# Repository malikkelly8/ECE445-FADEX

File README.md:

# FadeX - Automated Nicotine Tapering System

FadeX is an adaptive nicotine tapering prototype developed for ECE 445. The project explores a safer, feedback-based way to reduce nicotine concentration over time while preserving the user's familiar puff routine. Instead of forcing large manual concentration jumps, FadeX uses puff behavior, user check-ins, and embedded control logic to calculate a gradual taper and prepare a target mixture.

## Team Members

- **Malik Kelly** - Tapering algorithm, app/chatbot interface, ESP32 integration support
- **Justin Leith** - Project management, mechanical design, optical sensing support
- **Ian Zentner** - MCU logic, PCB design, hardware integration

## Final Prototype Overview

The final FadeX prototype centers on a **Homebase ESP32** that coordinates communication, dosing logic, pump control, load-cell feedback, and concentration sensing. A simplified **Handheld ESP32** is used to record puff activity and send puff-session data to the homebase. The system was demonstrated using a nicotine surrogate rather than real nicotine for safety.

The final architecture includes:

- **Homebase Controller:** ESP32-based controller that runs the tapering algorithm, receives puff data, controls pumps, reads load cells, and manages safety logic.
- **Handheld Puff Input:** Simplified ESP32 handheld with a puff button that records puff count/session duration and sends data to the homebase through ESP-NOW.
- **Fluid Delivery System:** Peristaltic pumps used to deliver concentrate/surrogate and diluent into a mixing reservoir.
- **Load-Cell Feedback:** HX711 load-cell amplifiers used to tare containers and verify delivered liquid mass.
- **UNCS Concentration Sensing:** UV LED and photodiode circuitry used to support concentration feedback for the vitamin C/ascorbic acid surrogate.
- **User Interface:** Blynk dashboard and/or serial-based FadeX Chatbot used to display system state, collect check-in responses, and guide the demo flow.

## Tapering Algorithm

FadeX calculates the next concentration using puff behavior, treatment week, user survey feedback, and safety limits. The algorithm combines objective usage data with simple self-report inputs so that the taper can slow down or stabilize when relapse risk appears higher.

Core algorithm ideas:

- Puff count and puff duration are collected from the handheld or demo input.
- The user check-in classifies the session as `Better`, `Neutral`, `Struggling`, or `Worse`.
- Trigger questions are only asked when the user reports `Struggling` or `Worse`.
- Scenario codes classify the current user state and guide tapering behavior.
- The next concentration is safety-clamped before pump volumes are calculated.
- Pump delivery is verified using load-cell feedback instead of relying only on timed pumping.

Example equations:

```text
A = 1.0 + S + (1.0 - Mu)
C_next = clamp(C_current - 0.28A, 0.5%, 5.0%)
V_concentrate = (C_next / 5.0) * V_total
V_diluent = V_total - V_concentrate
```

## Repository Structure

```text
/Code/              Firmware sketches, tests, and integration code
/Images/            Diagrams, presentation graphics, screenshots, and verification visuals
/Notebook_Entries/  Chronological lab notebook entries and engineering logs
/PCB/          PCB schematics, pinout references, and hardware design files
```

Some folders may contain uploaded final report materials, figures, or archived versions of earlier designs.

## Key Subsystem Tests

The project was developed through modular tests before final integration:

- ESP32 programming and MAC address identification
- ESP-NOW handheld-to-homebase puff communication
- Pump direction, flow-rate, and volume delivery tests
- Load-cell calibration and tare verification
- Water-by-weight dispense testing
- UV LED PWM output testing
- Photodiode ADC readout testing
- Blynk dashboard and FadeX Chatbot workflow testing
- Final integrated dosing and demo flow testing

## Safety Notes

The course prototype used water and vitamin C/ascorbic acid surrogate solutions instead of nicotine for safety. The firmware and demo flow include safety-oriented behavior such as load-cell taring, staged pump pulses, maximum mixing-volume checks, and emergency stop commands. The homebase controller is responsible for safety-critical pump control rather than relying only on the app interface.

## Project Tracking and Engineering Notebook

- `/Notebook_Entries/` contains chronological lab notebook entries documenting objectives, design decisions, testing, debugging, and final outcomes.
- `/Images/` contains visuals used for reports, slides, flowcharts, and verification documentation.
- The GitHub Project/Kanban board was used during development to track subsystem progress and remaining demo tasks.

## Final Deliverables

Final project materials include the final paper, video assignment, lab notebook entries, subsystem test code, algorithm visuals, and final demo documentation.

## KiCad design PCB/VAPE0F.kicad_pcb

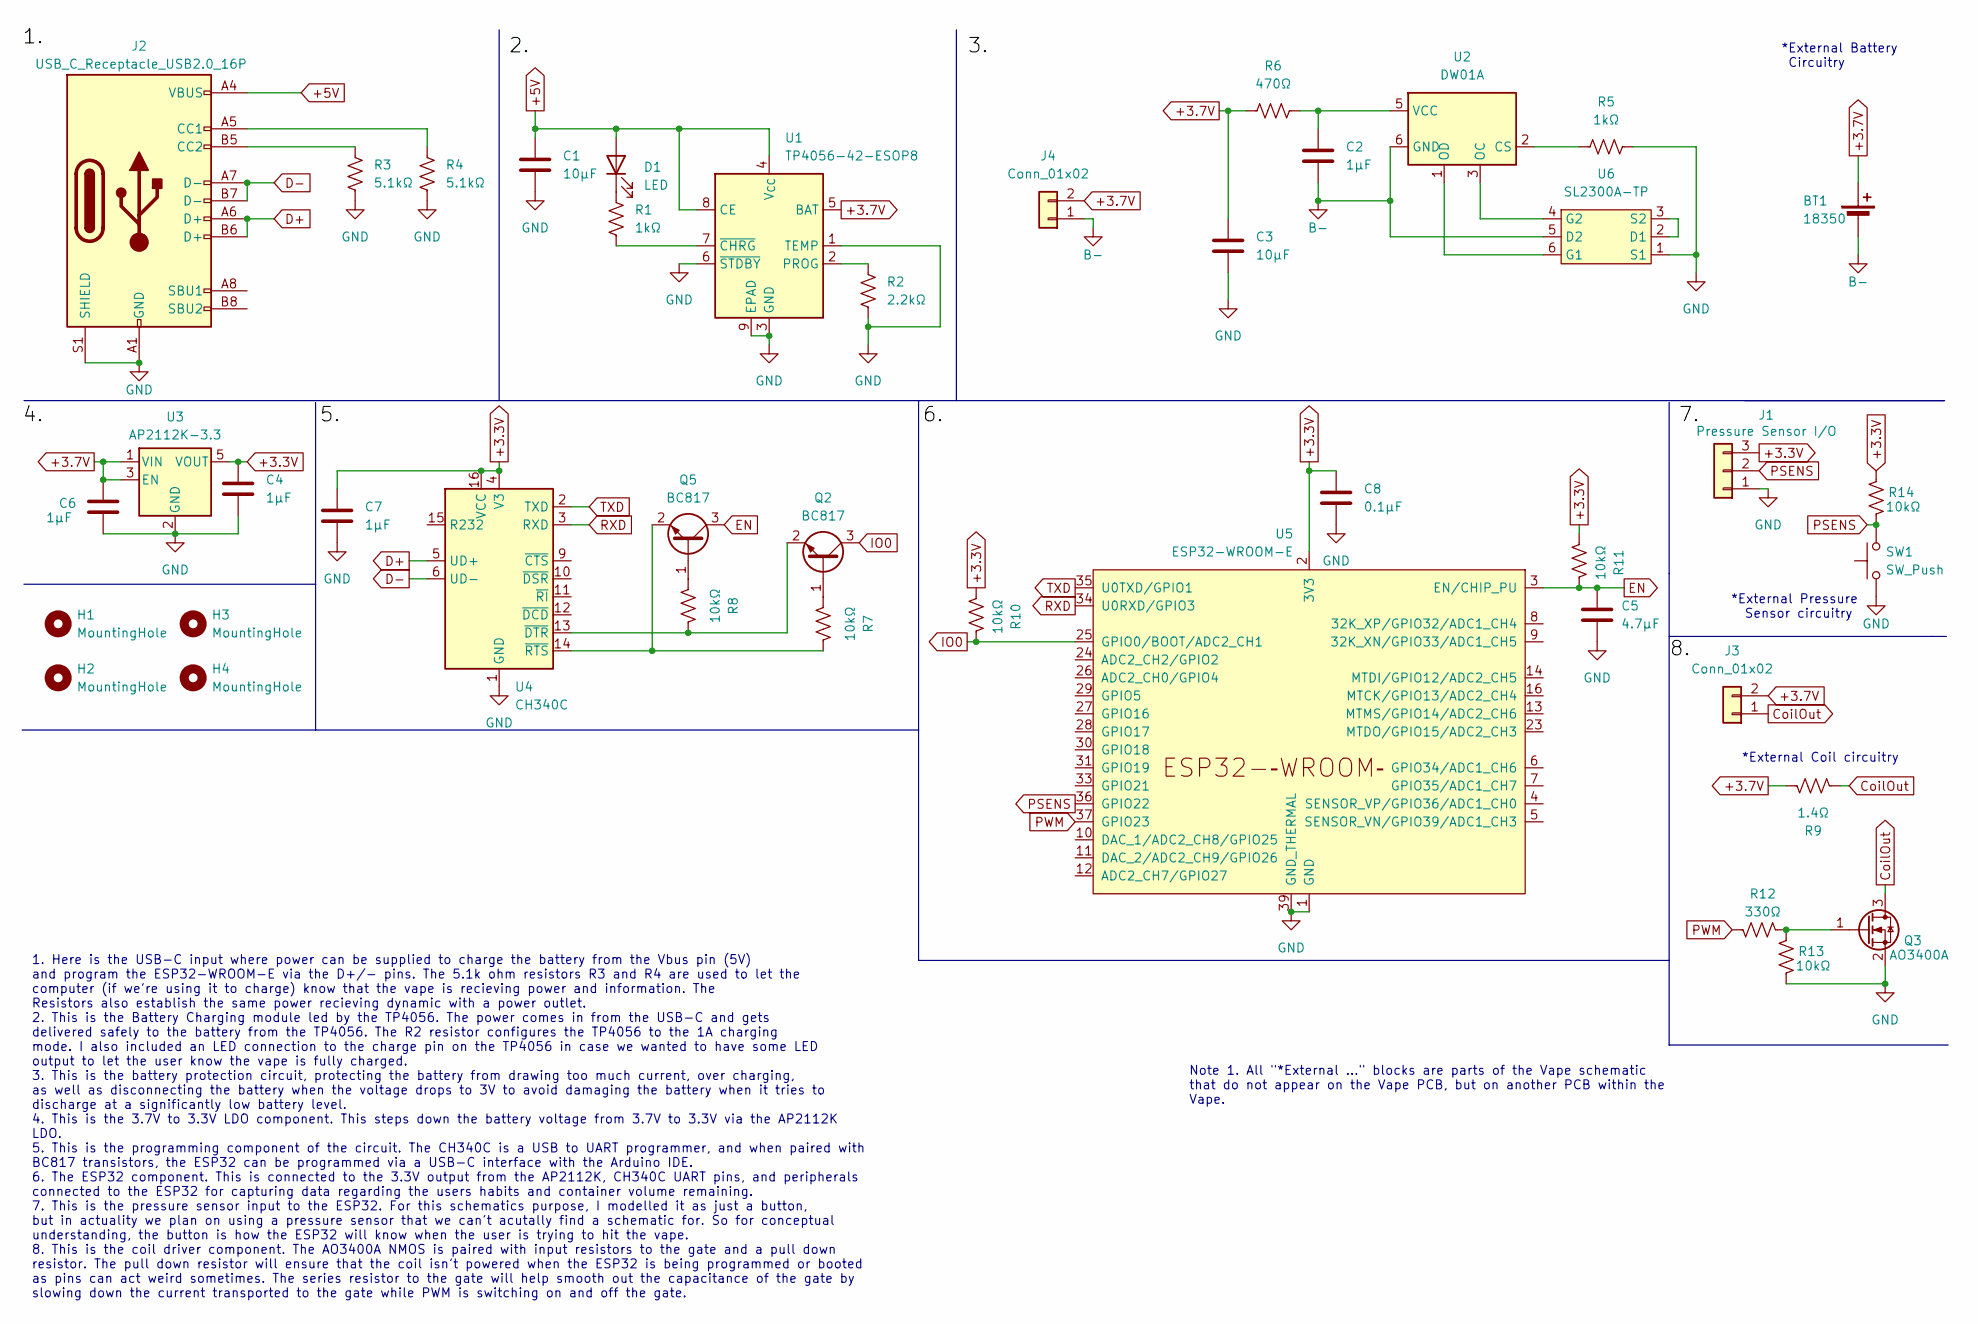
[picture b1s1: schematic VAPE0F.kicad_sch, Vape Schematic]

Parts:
BT1: 18350
C1, C3: 10μF; C_0805_2012Metric_Pad1.18x1.45mm_HandSolder
C2, C4, C6, C7: 1μF; C_0805_2012Metric_Pad1.18x1.45mm_HandSolder
C5: 4.7μF; C_0805_2012Metric_Pad1.18x1.45mm_HandSolder
C8: 0.1μF; C_0805_2012Metric_Pad1.18x1.45mm_HandSolder
D1: LED; LED_0805_2012Metric_Pad1.15x1.40mm_HandSolder
H1, H2, H3, H4: MountingHole; MountingHole_3.2mm_M3
J1: Pressure Sensor I/O; Molex_KK-254_AE-6410-03A_1x03_P2.54mm_Vertical
J2: USB_C_Receptacle_USB2.0_16P; USB_C_Receptacle_HRO_TYPE-C-31-M-12
J3, J4: Conn_01x02; Molex_KK-254_AE-6410-02A_1x02_P2.54mm_Vertical
Q2, Q5: BC817; SOT-23
Q3: AO3400A; SOT-23
R1, R5: 1kΩ; R_0805_2012Metric_Pad1.20x1.40mm_HandSolder
R2: 2.2kΩ; R_0805_2012Metric_Pad1.20x1.40mm_HandSolder
R3, R4: 5.1kΩ; R_0805_2012Metric_Pad1.20x1.40mm_HandSolder
R6: 470Ω; R_0805_2012Metric_Pad1.20x1.40mm_HandSolder
R7, R8, R10, R11, R13, R14: 10kΩ; R_0805_2012Metric_Pad1.20x1.40mm_HandSolder
R9: 1.4Ω; R_0805_2012Metric_Pad1.20x1.40mm_HandSolder
R12: 330Ω; R_0805_2012Metric_Pad1.20x1.40mm_HandSolder
SW1: SW_Push
U1: TP4056-42-ESOP8; SOIC-8-1EP_3.9x4.9mm_P1.27mm_EP2.41x3.3mm_ThermalVias
U2: DW01A; SOT-23-6
U3: AP2112K-3.3; SOT-23-5
U4: CH340C; SOIC-16_3.9x9.9mm_P1.27mm
U5: ESP32-WROOM-E; ESP32-WROOM-32E
U6: SL2300A-TP; SOT-23-6_Handsoldering

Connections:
+3.3V: C4.1, C7.1, C8.1, J1.3, R10.2, R11.2, R14.2, U3.5 (VOUT), U4.4 (V3), U4.16 (VCC), U5.2 (3V3)
+3.7V: BT1.1 (+), C3.1, C6.1, J3.2, J4.2, R6.1, R9.1, U1.5 (BAT), U3.1 (VIN), U3.3 (EN)
+5V: C1.1, D1.2 (A), J2.A4 (VBUS), J2.A9 (VBUS), J2.B4 (VBUS), J2.B9 (VBUS), U1.4 (V_{CC}), U1.8 (CE)
B-: BT1.2 (-), C2.2, J4.1, U2.6 (GND), U6.5 (D2)
CoilOut: J3.1, Q3.3 (D), R9.2
D+: J2.A6 (D+), J2.B6 (D+), U4.5 (UD+)
D-: J2.A7 (D-), J2.B7 (D-), U4.6 (UD-)
EN: C5.1, Q5.3 (C), R11.1, U5.3 (EN/CHIP_PU)
GND: C1.2, C3.2, C4.2, C5.2, C6.2, C7.2, C8.2, J1.1, J2.A1 (GND), J2.A12 (GND), J2.B1 (GND), J2.B12 (GND), J2.S1 (SHIELD), Q3.2 (S), R2.2, R3.2, R4.2, R5.2, R13.1, SW1.1, U1.1 (TEMP), U1.3 (GND), U1.6 (~STDBY), U1.9 (EPAD), U3.2 (GND), U4.1 (GND), U5.1 (GND), U5.15 (GND), U5.38 (GND), U5.39 (GND_THERMAL), U6.1 (S1)
IO0: Q2.3 (C), R10.1, U5.25 (GPIO0/BOOT/ADC2_CH1)
unnamed: D1.1 (K), R1.1
unnamed: J2.A5 (CC1), R4.1
unnamed: J2.B5 (CC2), R3.1
unnamed: Q2.1 (B), R7.2
unnamed: Q2.2 (E), R8.1, U4.13 (~DTR)
unnamed: Q3.1 (G), R12.2, R13.2
unnamed: Q5.1 (B), R8.2
unnamed: Q5.2 (E), R7.1, U4.14 (~RTS)
unnamed: R2.1, U1.2 (PROG)
unnamed: R1.2, U1.7 (~CHRG)
unnamed: R5.1, U2.2 (CS)
unnamed: U2.3 (OC), U6.4 (G2)
unnamed: U2.1 (OD), U6.6 (G1)
unnamed: C2.1, R6.2, U2.5 (VCC)
unnamed: U6.2 (D1), U6.3 (S2)
PSENS: J1.2, R14.1, SW1.2, U5.36 (GPIO22)
PWM: R12.1, U5.37 (GPIO23)
RXD: U4.3 (RXD), U5.34 (U0RXD/GPIO3)
TXD: U4.2 (TXD), U5.35 (U0TXD/GPIO1)

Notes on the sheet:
*External Coil circuitry
*External Battery Circuitry
1. Here is the USB-C input where power can be supplied to charge the battery from the Vbus pin (5V) and program the ESP32-WROOM-E via the D+/- pins. The 5.1k ohm resistors R3 and R4 are used to let the computer (if we're using it to charge) know that the vape is recieving power and information. The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
Note 1. All "*External ..." blocks are parts of the Vape schematic that do not appear on the Vape PCB, but on another PCB within the Vape.
*External Pressure Sensor circuitry

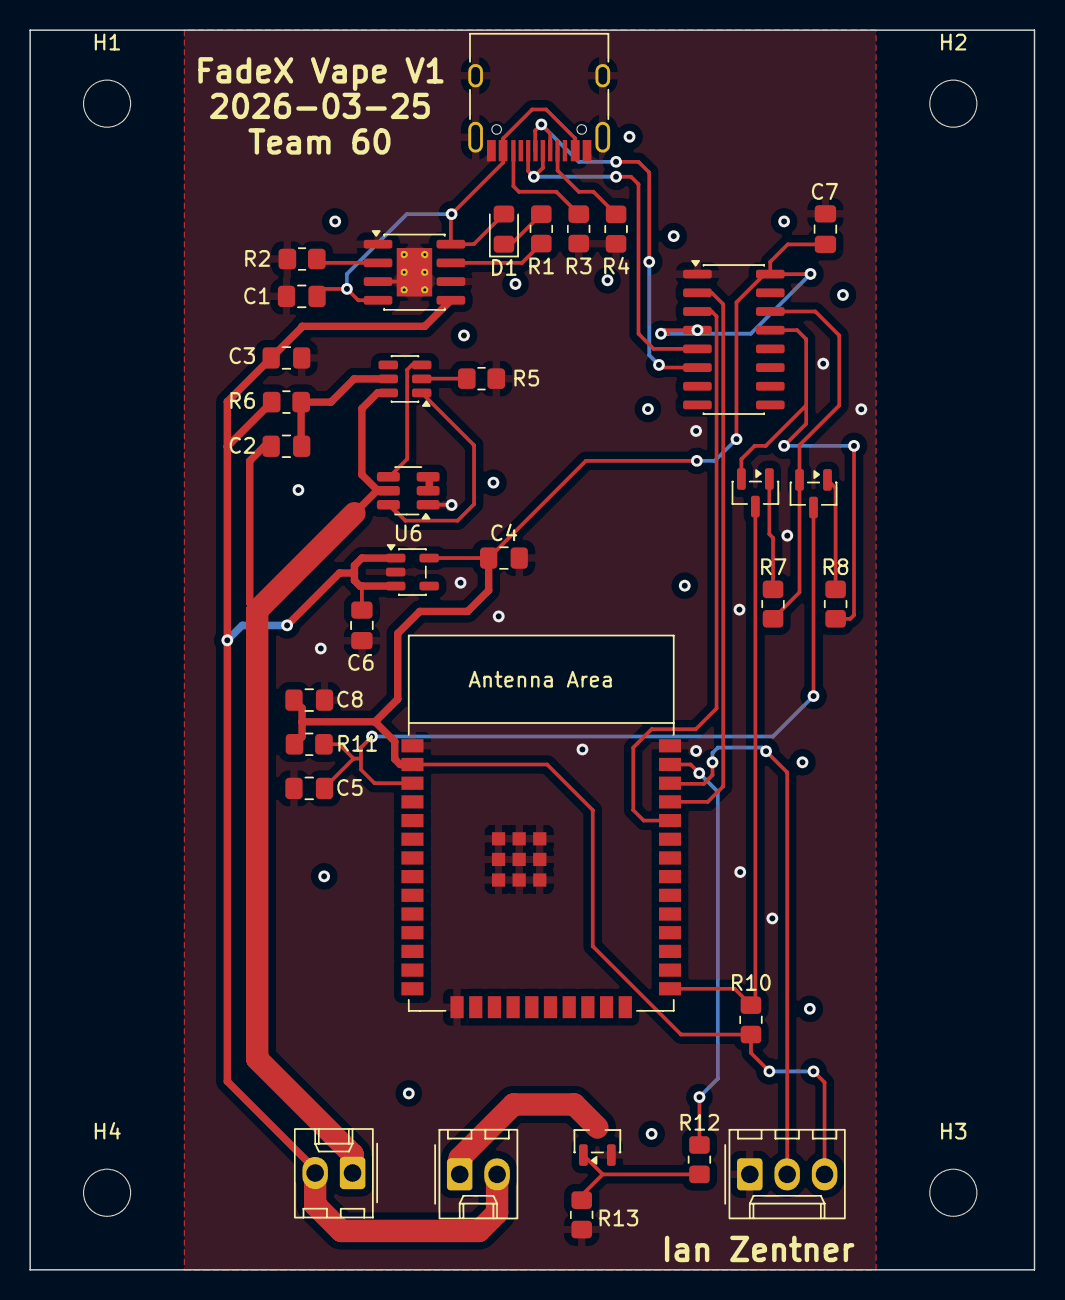
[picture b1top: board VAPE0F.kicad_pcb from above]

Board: 2 copper layers, 68.2 x 84.2 mm, 38 parts (0 on the bottom side), 29 nets.

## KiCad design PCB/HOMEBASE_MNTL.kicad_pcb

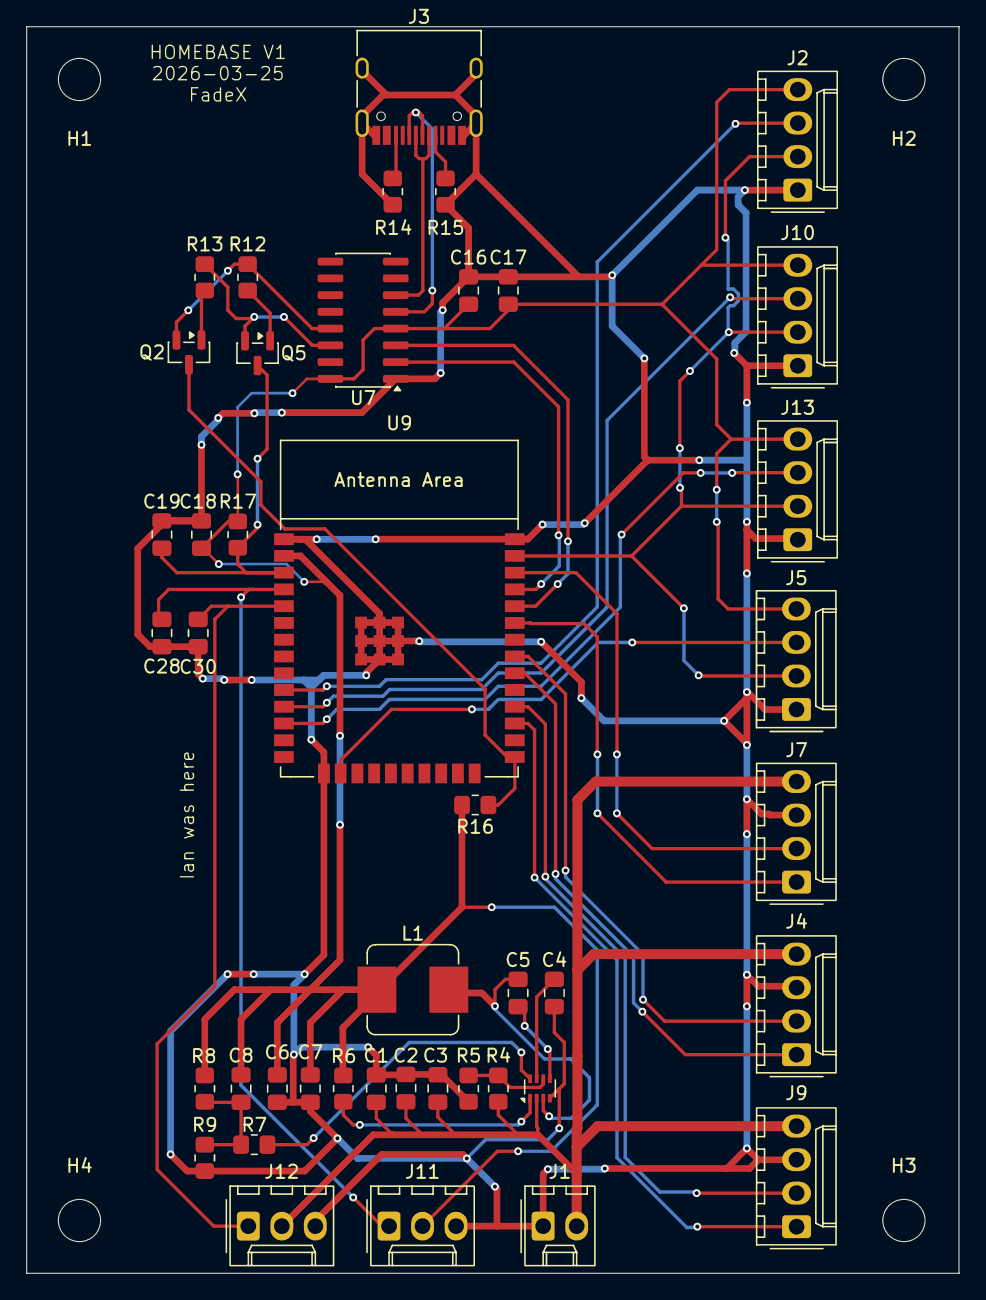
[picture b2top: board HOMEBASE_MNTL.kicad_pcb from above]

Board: 2 copper layers, 70.7 x 94.5 mm, 47 parts (0 on the bottom side), 36 nets.

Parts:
C1, C2: 10μF; C_0805_2012Metric_Pad1.18x1.45mm_HandSolder
C3, C5, C18: 0.1μF; C_0805_2012Metric_Pad1.18x1.45mm_HandSolder
C4: 22nF; C_0805_2012Metric_Pad1.18x1.45mm_HandSolder
C6, C7: 22μF; C_0805_2012Metric_Pad1.18x1.45mm_HandSolder
C8: 470pF; C_0805_2012Metric_Pad1.18x1.45mm_HandSolder
C16, C17, C28, C30: 1μF; C_0805_2012Metric_Pad1.18x1.45mm_HandSolder
C19: 4.7μF; C_0805_2012Metric_Pad1.18x1.45mm_HandSolder
H1, H2, H3, H4: MountingHole; MountingHole_3.2mm_M3
J1: Conn_01x02; Molex_KK-254_AE-6410-02A_1x02_P2.54mm_Vertical
J2: Load Cell 1 Con.; Molex_KK-254_AE-6410-04A_1x04_P2.54mm_Vertical
J3: USB_C_Receptacle_USB2.0_16P; USB_C_Receptacle_HRO_TYPE-C-31-M-12
J4: Pump 2 Con.; Molex_KK-254_AE-6410-04A_1x04_P2.54mm_Vertical
J5: Load Cell 4 Con.; Molex_KK-254_AE-6410-04A_1x04_P2.54mm_Vertical
J7: Pump 1 Con.; Molex_KK-254_AE-6410-04A_1x04_P2.54mm_Vertical
J9: Pump 3 Con.; Molex_KK-254_AE-6410-04A_1x04_P2.54mm_Vertical
J10: Load Cell 2 Con.; Molex_KK-254_AE-6410-04A_1x04_P2.54mm_Vertical
J11: Photodiode Con.; Molex_KK-254_AE-6410-03A_1x03_P2.54mm_Vertical
J12: UVLED Con.; Molex_KK-254_AE-6410-03A_1x03_P2.54mm_Vertical
J13: Load Cell 3 Con.; Molex_KK-254_AE-6410-04A_1x04_P2.54mm_Vertical
L1: 6.8μH; L_Bourns_SRP7028A_7.3x6.6mm
Q2, Q5: BC817; SOT-23
R4: 191kΩ; R_0805_2012Metric_Pad1.20x1.40mm_HandSolder
R5: 49.9kΩ; R_0805_2012Metric_Pad1.20x1.40mm_HandSolder
R6: 100kΩ; R_0805_2012Metric_Pad1.20x1.40mm_HandSolder
R7, R12, R13, R16, R17: 10kΩ; R_0805_2012Metric_Pad1.20x1.40mm_HandSolder
R8: 51kΩ; R_0805_2012Metric_Pad1.20x1.40mm_HandSolder
R9: 9.09kΩ; R_0805_2012Metric_Pad1.20x1.40mm_HandSolder
R14, R15: 5.1kΩ; R_0805_2012Metric_Pad1.20x1.40mm_HandSolder
U2: MP2338GTL-P; SOT-583-8
U7: CH340C; SOIC-16_3.9x9.9mm_P1.27mm
U9: ESP32-WROOM-E; ESP32-WROOM-32E

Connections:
3.3V: C6.1, C7.1, C8.2, C16.1, C17.1, C18.1, J2.4, J5.4, J10.4, J11.2, J13.4, L1.2, R6.2, R8.2, R16.2, R17.2, U7.4 (V3), U7.16 (VCC), U9.2 (3V3)
12V: C1.1, C2.1, C3.1, J1.2, J4.4, J7.4, J9.4, J12.2, R4.1, U2.2 (VIN)
3190.1.IN1: J7.2, U9.36 (GPIO22)
3190.1.IN2: J7.1, U9.33 (GPIO21)
3190.2.IN1: J4.2, U9.31 (GPIO19)
3190.2.IN2: J4.1, U9.30 (GPIO18)
3190.3.IN1: J9.2, U9.28 (GPIO17)
3190.3.IN2: J9.1, U9.27 (GPIO16)
BST.3_3V: C5.1, U2.5 (BST)
D+: J3.A6 (D+), J3.B6 (D+), U7.5 (UD+)
D-: J3.A7 (D-), J3.B7 (D-), U7.6 (UD-)
DAT1: J2.3, U9.10 (DAC_1/ADC2_CH8/GPIO25)
DAT2: J10.3, U9.11 (DAC_2/ADC2_CH9/GPIO26)
DAT3: J13.3, U9.12 (ADC2_CH7/GPIO27)
DAT4: J5.3, U9.16 (MTCK/GPIO13/ADC2_CH4)
EN: C19.1, Q5.3 (C), R17.1, U9.3 (EN/CHIP_PU)
EN.3_3V: R4.2, R5.1, U2.6 (EN)
FB.3_3V: R7.1, U2.8 (FB)
GND: C1.2, C2.2, C3.2, C4.2, C6.2, C7.2, C16.2, C17.2, C18.2, C19.2, C28.2, C30.2, J1.1, J2.1, J3.A1 (GND), J3.A12 (GND), J3.B1 (GND), J3.B12 (GND), J3.S1 (SHIELD), J4.3, J5.1, J7.3, J9.3, J10.1, J11.3, J12.3, J13.1, R5.2, R9.2, R14.2, R15.2, U2.4 (GND), U7.1 (GND), U9.1 (GND), U9.15 (GND), U9.38 (GND), U9.39 (GND_THERMAL)
IO0: Q2.3 (C), R16.1, U9.25 (GPIO0/BOOT/ADC2_CH1)
unnamed: C8.1, R7.2, R8.1, R9.1
unnamed: J3.A5 (CC1), R15.1
unnamed: J3.B5 (CC2), R14.1
unnamed: J3.A4 (VBUS), J3.A9 (VBUS), J3.B4 (VBUS), J3.B9 (VBUS)
unnamed: Q2.1 (B), R13.2
unnamed: Q2.2 (E), R12.1, U7.13 (~DTR)
unnamed: Q5.1 (B), R12.2
unnamed: Q5.2 (E), R13.1, U7.14 (~RTS)
unnamed: C4.1, U2.7 (SS)
PDO: C28.1, J11.1, U9.4 (SENSOR_VP/GPIO36/ADC1_CH0)
PG.3_3V: R6.1, U2.1 (PG)
RXD: U7.3 (RXD), U9.34 (U0RXD/GPIO3)
SCLK: J2.2, J5.2, J10.2, J13.2, U9.37 (GPIO23)
SW.3_3V: C5.2, L1.1, U2.3 (SW)
TXD: U7.2 (TXD), U9.35 (U0TXD/GPIO1)
UVLEDPWM: C30.1, J12.1, U9.5 (SENSOR_VN/GPIO39/ADC1_CH3)

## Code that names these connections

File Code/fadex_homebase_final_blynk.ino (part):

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};

// Final PCB pump-driver wiring:
// Pump 1 (nicotine) -> IN1 GPIO22, IN2 GPIO21
// Pump 2 (diluent)  -> IN1 GPIO19, IN2 GPIO18
// Pump 3 (mixing)   -> IN1 GPIO33, IN2 GPIO4
constexpr PumpChannel NICOTINE_PUMP = {22, 21, "Nicotine"};
constexpr PumpChannel DILUENT_PUMP = {19, 18, "Diluent"};
constexpr PumpChannel MIXING_PUMP = {33, 4, "Mixing"};

// Final PCB load-cell wiring:
// Shared HX711 clock -> GPIO23
// Data lines -> GPIO25, GPIO26, GPIO27, GPIO13
constexpr int HX711_SCK_PIN = 23;
constexpr int HX711_DATA1_PIN = 25;
constexpr int HX711_DATA2_PIN = 26;
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
// UNCS optical sensor wiring:
// PDO is the photodiode/TIA output into ESP32 ADC1_CH0.
// UVLEDPWM needs an output-capable pin. The PCB net was originally tied to
// GPIO39, which is input-only, so the demo assumes the jumper to GPIO32.
constexpr int UNCS_PHOTODIODE_ADC_PIN = 36;
constexpr int UNCS_UV_LED_PWM_PIN = 32;
constexpr uint8_t UNCS_PWM_CHANNEL = 0;
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  setUncsLed(false);

  Serial.println("UNCS optical sensor initialized.");
  Serial.print("  Photodiode PDO ADC: GPIO");
  Serial.println(UNCS_PHOTODIODE_ADC_PIN);
  Serial.print("  UV LED PWM output: GPIO");
  Serial.println(UNCS_UV_LED_PWM_PIN);
  Serial.println("  Note: UVLEDPWM needs the GPIO32 jumper because GPIO39 is input-only.");
}

float readUncsPhotodiodeVoltage() {
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  Serial.println();
  Serial.println("FadeX final homebase with Blynk");
  Serial.println("PCB pump pins:");
  Serial.println("  Pump 1 (Nicotine): IN1 GPIO22, IN2 GPIO21");
  Serial.println("  Pump 2 (Diluent):  IN1 GPIO19, IN2 GPIO18");
  Serial.println("  Pump 3 (Mixing):   IN1 GPIO33, IN2 GPIO4");
  Serial.println("PCB load-cell pins:");
  Serial.println("  HX711 SCLK: GPIO23");
  Serial.println("  LCA1 DATA: GPIO25");
  Serial.println("  LCA2 DATA: GPIO26");
  Serial.println("  LCA3 DATA: GPIO27");
  Serial.println("  LCA4 DATA: GPIO13");
  Serial.println();
  Serial.println("Virtual Pin map:");
  Serial.println("  V0  Current Concentration");
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  Serial.println("  V28 UNCS Vitamin C Concentration mM (optional)");
  Serial.println();
  Serial.println("UNCS optical sensor:");
  Serial.println("  PDO photodiode ADC: GPIO36");
  Serial.println("  UV LED PWM: GPIO32 jumper to UVLEDPWM");
  Serial.println("  Emergency stop commands: STOP, ESTOP, ABORT, or S");
  Serial.println("  Commands: UV ON, UV OFF, UV DUTY <0-100>, UV READ, UV STREAM ON/OFF");
  Serial.println("            UNCS DARK, UNCS BLANK, UNCS SAMPLE, UNCS STATUS");
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
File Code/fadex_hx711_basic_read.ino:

#include <Arduino.h>
#include "HX711.h"

// HX711 basic read sketch adapted for the FadeX homebase ESP32.
//
// We would use this after the calibration sketch once we found a good
// calibration factor for our specific TAL221 + HX711 setup.
//
// PCB connector map:
//   J2  Load Cell 1 connector -> DAT1 / GPIO25
//   J10 Load Cell 2 connector -> DAT2 / GPIO26
//   J13 Load Cell 3 connector -> DAT3 / GPIO27
//   J5  Load Cell 4 connector -> DAT4 / GPIO13
//   All four connectors share SCLK / GPIO23
//
// Set ACTIVE_LOAD_CELL to whichever channel you want to verify.

constexpr int HX711_SCK = 23;
constexpr int LOADCELL_DATA_PINS[] = {25, 26, 27, 13};
constexpr const char *LOADCELL_NAMES[] = {"LCA1", "LCA2", "LCA3", "LCA4"};
constexpr const char *LOADCELL_CONNECTORS[] = {"J2", "J10", "J13", "J5"};
constexpr const char *LOADCELL_DATA_NETS[] = {"DAT1", "DAT2", "DAT3", "DAT4"};
constexpr int LOADCELL_ESP32_MODULE_PINS[] = {10, 11, 12, 16};
constexpr int HX711_SCK_ESP32_MODULE_PIN = 37;

constexpr int ACTIVE_LOAD_CELL = 4;
constexpr int HX711_DOUT = LOADCELL_DATA_PINS[ACTIVE_LOAD_CELL - 1];
constexpr const char *ACTIVE_LOAD_CELL_NAME = LOADCELL_NAMES[ACTIVE_LOAD_CELL - 1];
constexpr const char *ACTIVE_LOAD_CELL_CONNECTOR = LOADCELL_CONNECTORS[ACTIVE_LOAD_CELL - 1];
constexpr const char *ACTIVE_LOAD_CELL_DATA_NET = LOADCELL_DATA_NETS[ACTIVE_LOAD_CELL - 1];
constexpr int ACTIVE_LOAD_CELL_ESP32_MODULE_PIN = LOADCELL_ESP32_MODULE_PINS[ACTIVE_LOAD_CELL - 1];

// Replace this with the value you found for the selected load cell.
constexpr float CALIBRATION_FACTOR = 2925.40f;

HX711 scale;

void tareScale() {
  Serial.println("Leave the load cell completely untouched. Taring...");
  delay(1500);
  scale.set_scale();
  scale.tare(20);
  scale.set_scale(CALIBRATION_FACTOR);
  delay(250);
  Serial.println("Tare complete.");
}

void setup() {
  Serial.begin(115200);
  delay(300);

  Serial.println();
  Serial.println("HX711 basic read sketch for FadeX PCB");
  Serial.print("Active load cell: ");
  Serial.println(ACTIVE_LOAD_CELL_NAME);
  Serial.print("PCB connector: ");
  Serial.println(ACTIVE_LOAD_CELL_CONNECTOR);
  Serial.print("HX711 data net: ");
  Serial.println(ACTIVE_LOAD_CELL_DATA_NET);
  Serial.print("DOUT Arduino pin: GPIO");
  Serial.println(HX711_DOUT);
  Serial.print("DOUT ESP32 module pin: ");
  Serial.println(ACTIVE_LOAD_CELL_ESP32_MODULE_PIN);
  Serial.print("Shared SCK Arduino pin: GPIO");
  Serial.println(HX711_SCK);
  Serial.print("Shared SCK ESP32 module pin: ");
  Serial.println(HX711_SCK_ESP32_MODULE_PIN);

  scale.begin(HX711_DOUT, HX711_SCK);

  if (!scale.is_ready()) {
    Serial.println("HX711 is not ready. Check power, ground, DOUT, and SCK.");
    return;
  }

  tareScale();

  Serial.println("Readings:");
  Serial.println("Press 't' to tare again.");
}

void loop() {
  if (!scale.is_ready()) {
    Serial.println("HX711 not ready.");
    delay(500);
    return;
  }

  if (Serial.available() > 0) {
    char input = static_cast<char>(Serial.read());
    if (input == 't' || input == 'T') {
      tareScale();
    }
  }

  const long raw = scale.read_average(3);
  const float reading = scale.get_units(5);

  Serial.print("Raw: ");
  Serial.print(raw);
  Serial.print(" | Reading: ");
  Serial.print(reading, 2);
  Serial.print(" | calibration_factor: ");
  Serial.println(CALIBRATION_FACTOR, 2);

  delay(250);
}

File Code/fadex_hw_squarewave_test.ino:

#include <Arduino.h>

// This sketch outputs a continuous 50% duty-cycle square wave on one GPIO.
// Use it to verify that:
// 1. the ESP32 can be programmed successfully, and
// 2. the chosen output pin is really connected where you think it is.
//
// Probe the selected TEST_GPIO with an oscilloscope after upload.
// The scope should show a square wave at SQUARE_WAVE_HZ.
//
// Important note:
// The "27, 28, 31, 30, 33, 36" numbers from the ESP32-WROOM schematic
// are module pin numbers, not Arduino GPIO numbers.
// Those map to:
//   module pin 27 -> GPIO16
//   module pin 28 -> GPIO17
//   module pin 31 -> GPIO19
//   module pin 30 -> GPIO18
//   module pin 33 -> GPIO21
//   module pin 36 -> GPIO22

constexpr int TEST_GPIO = 16;
constexpr uint32_t SQUARE_WAVE_HZ = 1000;
constexpr uint8_t LEDC_CHANNEL = 0;
constexpr uint8_t LEDC_RESOLUTION_BITS = 8;

void setup() {
  Serial.begin(115200);
  delay(300);

  Serial.println();
  Serial.println("FadeX square-wave GPIO test");
  Serial.print("Output GPIO: ");
  Serial.println(TEST_GPIO);
  Serial.print("Frequency (Hz): ");
  Serial.println(SQUARE_WAVE_HZ);
  Serial.println("Probe this pin with the oscilloscope.");

  ledcSetup(LEDC_CHANNEL, SQUARE_WAVE_HZ, LEDC_RESOLUTION_BITS);
  ledcAttachPin(TEST_GPIO, LEDC_CHANNEL);

  // 50% duty cycle for a clean square wave.
  ledcWrite(LEDC_CHANNEL, 128);
}

void loop() {
  // Nothing else to do. The hardware PWM peripheral keeps the square wave running.
  delay(1000);
}

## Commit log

2026-02-03 Mission Statement
2026-03-02 Initialize README with project details
    Added project overview, team members, and repository structure.
2026-03-02 Update team members section in README
2026-03-02 Add notebook entry for February 26, 2026
    Documented algorithm design, software architecture, and test results for the volumetric dilution logic and BLE application setup.
2026-03-02 Add entry for February 26, 2026 by Malik Kelly
2026-05-06 Add notebook entry for FadeX project evaluation
    Documented the evaluation of the FadeX project concept, including objectives, work completed, results, decisions, next steps, and a suggested figure.
2026-05-06 Update and rename Week of 2-2-26 to 2-2-26
2026-05-06 Rename 2-2-26 to 2-2-26.md
2026-05-06 Update project notes with next steps and figure
    Added next steps and suggested figure for the project.
2026-05-06 Enhance project entry with objectives and work details
    Added additional context to the project direction and system planning entry, including objectives and work completed.
2026-05-06 Add entry for early risk identification and project planning
2026-05-06 Add subsystem breakdown entry for FadeX design
    Documented the subsystem breakdown and interactions for the FadeX device design, including objectives, work completed, results, decisions, and next steps.
2026-05-06 Correct figure caption format in notebook entry
2026-05-06 Add tolerance analysis entry for fluid delivery risks
    Documented tolerance analysis and fluid delivery risks for nicotine concentration control in vaping devices. Included objectives, work completed, results, decisions, next steps, and a supporting figu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
2026-05-06 Update project notes by removing figure suggestion
    Removed suggested figure description from the notes.
2026-05-06 Add notebook entry for component sourcing planning
2026-05-06 Rename 2-16-26.md to 2-14-26.md
2026-05-06 Update entry date and refine content in notebook
2026-05-06 Add team contract and role planning entry
2026-05-06 Add PCB review preparation entry
    Documented preparation for PCB review, including objectives, completed work, decisions made, and next steps.
2026-05-06 Modify figure caption for FadeX Home Base
    Updated figure caption to include Handheld Vaporizer.
2026-05-06 Update entry on control and safety logic design
    Removed suggested figure and adjusted formatting.
2026-05-06 Add entry on fluid mixing and concentration control
    Documented fluid-mixing equations and tolerance analysis for nicotine concentration control. Included calculations and results supporting the feasibility of pump-based mixing.
2026-05-06 Document cost, schedule, and safety for design
    Added detailed cost analysis, schedule planning, safety procedures, and engineering standards to the design document.
2026-05-06 Add design document submission entry
    Documented the design document submission and review preparation process, including objectives, work completed, results, and next steps.
2026-05-06 Refine design review entry and update next steps
2026-05-06 Add notebook entry for PCB planning and parts ordering
    Documented PCB planning and parts ordering process, including objectives, work completed, decisions made, and next steps.
2026-05-06 Document verification planning for breadboard demo
    Added details about verification planning for the breadboard demo, including objectives, work completed, and next steps.
2026-05-06 Add notebook entry for breadboard demo planning
2026-05-06 Update meeting date from 3/9/26 to 3/10/26
2026-05-06 Update entry on pump and chemical strategy
2026-05-06 Add spring break work planning entry
    Documented planning for spring break work to maintain project progress.
2026-05-06 Add notebook entry for spring break remote planning
    Documented spring break planning activities and decisions.
2026-05-06 Add entry on algorithm refinement and user data
    Documented algorithm direction and user data planning for FadeX tapering.
2026-05-06 Add user interaction planning entry for FadeX app
    Documented planning for user interaction with the FadeX app, including objectives, work completed, decisions made, and next steps.
2026-05-06 Document PCB order and hardware planning details
    Added details about PCB ordering and hardware planning.
2026-05-06 Add documentation for adaptive tapering algorithm
    Documented the adaptive tapering algorithm with a focus on visualization and explanation for future reports. Included details on the algorithm's major steps and decisions made regarding its presentat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
2026-05-06 Add entry for breadboard-to-PCB transition planning
    Documented planning for transitioning from breadboard to PCB testing, including objectives, work completed, results, and next steps.
2026-05-06 Add progress report entry for 3-30-26
    Documented individual progress report preparation, including contributions, project status, and next steps.
2026-05-06 Add entry on GitHub and Kanban board coordination
    Documented team discussions on GitHub access and Kanban board usage for project coordination.
2026-05-06 Add entry on verification and flowchart planning
    Documented verification planning and flowchart organization for the FadeX algorithm, including subsystem integration and verification tests.
2026-05-06 Update entry date from 3/30/26 to 3/31/26
2026-05-06 Add mock demo planning entry to notebook
    Documented planning and review for mock demo, including objectives, completed work, decisions made, and next steps.
2026-05-06 Add test planning entry for skeleton code
    Documented test planning for skeleton code to verify hardware functionality before system integration.
2026-05-06 Add entry for Blynk app planning on 4/15/26
    Documented planning for Blynk app dashboard and user interface for the FadeX demo, including objectives, completed work, decisions made, and next steps.
2026-05-06 Add entry on parts procurement and nicotine planning
    Documented parts procurement issues and contingency planning regarding nicotine use in the lab.
2026-05-06 Add mock demo preparation entry for 4/20/26
    Documented the preparation and outcomes of the mock demo, including objectives, work completed, results, and next steps.
2026-05-06 Add entry for mock presentation slide planning
    Documented mock presentation planning for project objectives and algorithm flow.
2026-05-06 Create entry for algorithm and stage visuals
    Added detailed entry about algorithm and stage visual development for project presentation.
2026-05-06 Add demo flow entry for Blynk and FadeX Chatbot
    Documented the demo flow using Blynk and the FadeX Chatbot, detailing objectives, work completed, results, and next steps.
2026-05-06 Add final demo risk review entry
    Documented the final demo risk review, outlining objectives, work completed, results, and next steps.
2026-05-06 Add entry for final demo setup on 4/27/26
    Documented the final demo setup and system readiness for the FadeX prototype, including objectives and completed work.
2026-05-06 Add final demonstration entry for FadeX system
    Added a new entry documenting the final demonstration of the FadeX system, including objectives, work completed, results, and next steps.
2026-05-06 Add final presentation preparation entry
    Documented the final presentation preparation, including objectives, work completed, results, and next steps.
2026-05-06 Add final presentation entry for FadeX project
    Documented final presentation details and feedback for the FadeX project, including objectives, work completed, results, and next steps.
2026-05-06 Add final paper and video assignment entry
    Documented final paper and video assignment work, including updates to the design document and preparation for submission.
2026-05-06 Create handheld
2026-05-07 Create Algorithm
2026-05-07 Remove suggested figure from notebook entry
    Removed suggested figure description for design comparison.
2026-05-07 Project Direction and System Planning
2026-05-07 Initial FadeX Feasibility Discussion
2026-05-07 Early Risk Identification
    Removed suggested figure reference from the notebook entry.
2026-05-07 Proposal Planning and High-Level Requirements
2026-05-07 System Block Diagram and Subsystem Breakdown
2026-05-07 Revise README with detailed project information
    Expanded project overview, team roles, and detailed prototype architecture. Added sections on tapering algorithm, repository structure, subsystem tests, safety notes, and final deliverables.
2026-05-07 Update README to remove folder references
    Removed references to Software, CAD, and Datasheets folders.
2026-05-07 Algorithm Direction and User Data Planning
    Removed suggested figure reference from the notebook entry.
2026-05-07 App Interface and User Interaction Planning
2026-05-07 Post-Break Hardware Bring-Up Plan
    Removed suggested figure reference from the notebook entry.
2026-05-07 Post-Spring-Break Project Reset
    Removed suggested figure for post-spring-break task board.
2026-05-07 PCB Order and Hardware Availability Planning
    Removed the suggested figure reference for PCB pinout planning.
2026-05-07 Algorithm Flowchart and Documentation Update
2026-05-07 Remove suggested figure from notebook entryBreadboard-to-PCB Transition Planning
    Removed suggested figure description from the notebook entry.
2026-05-07 Breadboard-to-PCB Transition Planning
2026-05-07 Individual Progress Report Preparation
    Removed suggested figure description from the notebook entry.
2026-05-07 GitHub Repository and Kanban Access
    Removed suggested figure reference from the entry.
2026-05-07 Verification and Flowchart Planning
    Removed suggested figure description from the notebook entry.
2026-05-07 Hardware Testing Strategy and Breadboard Planning
    Removed suggested figure description from the notebook entry.
2026-05-07 Mock Demo Planning and Kanban Review
    Removed suggested figure reference from the entry.
2026-05-07 Skeleton Code Test Planning
    Removed suggested figure description from the notebook entry.
2026-05-07 Blynk App and User Interface Planning
    Removed suggested figure reference from the notebook entry.
2026-05-07 Parts Procurement and Nicotine Contingency Planning
    Removed suggested figure description from the notes.
2026-05-07 Mock Demo Preparation
    Removed suggested figure reference from the document.
2026-05-07 Mock Presentation Slide Planning
    Removed suggested figure description from the notebook entry.
2026-05-07 Algorithm and Stage Visual Development
2026-05-07 Blynk Dashboard and Chatbot Demo Flow
    Removed suggested figure description from the notebook entry.
2026-05-07 Final Demo Risk Review
    Removed suggested figure description from the notes.
2026-05-07 Final Demo Setup and System Readiness
2026-05-07 Final Demonstration Execution
    Removed suggested figure description for final demo results.
2026-05-07 Final Presentation Preparation
    Removed suggested figure description from the notes.
2026-05-07 Final Presentation and Feedback
    Removed suggestion for a figure in the final paper.
2026-05-07 Final Paper and Video Assignment Work
    Removed suggested figure description from the notebook entry.
2026-05-07 Create blank
2026-05-07 Revise Mission Statement for FadeX project
    Updated the mission statement to reflect the goals and technology of FadeX, emphasizing automated and personalized nicotine tapering.
